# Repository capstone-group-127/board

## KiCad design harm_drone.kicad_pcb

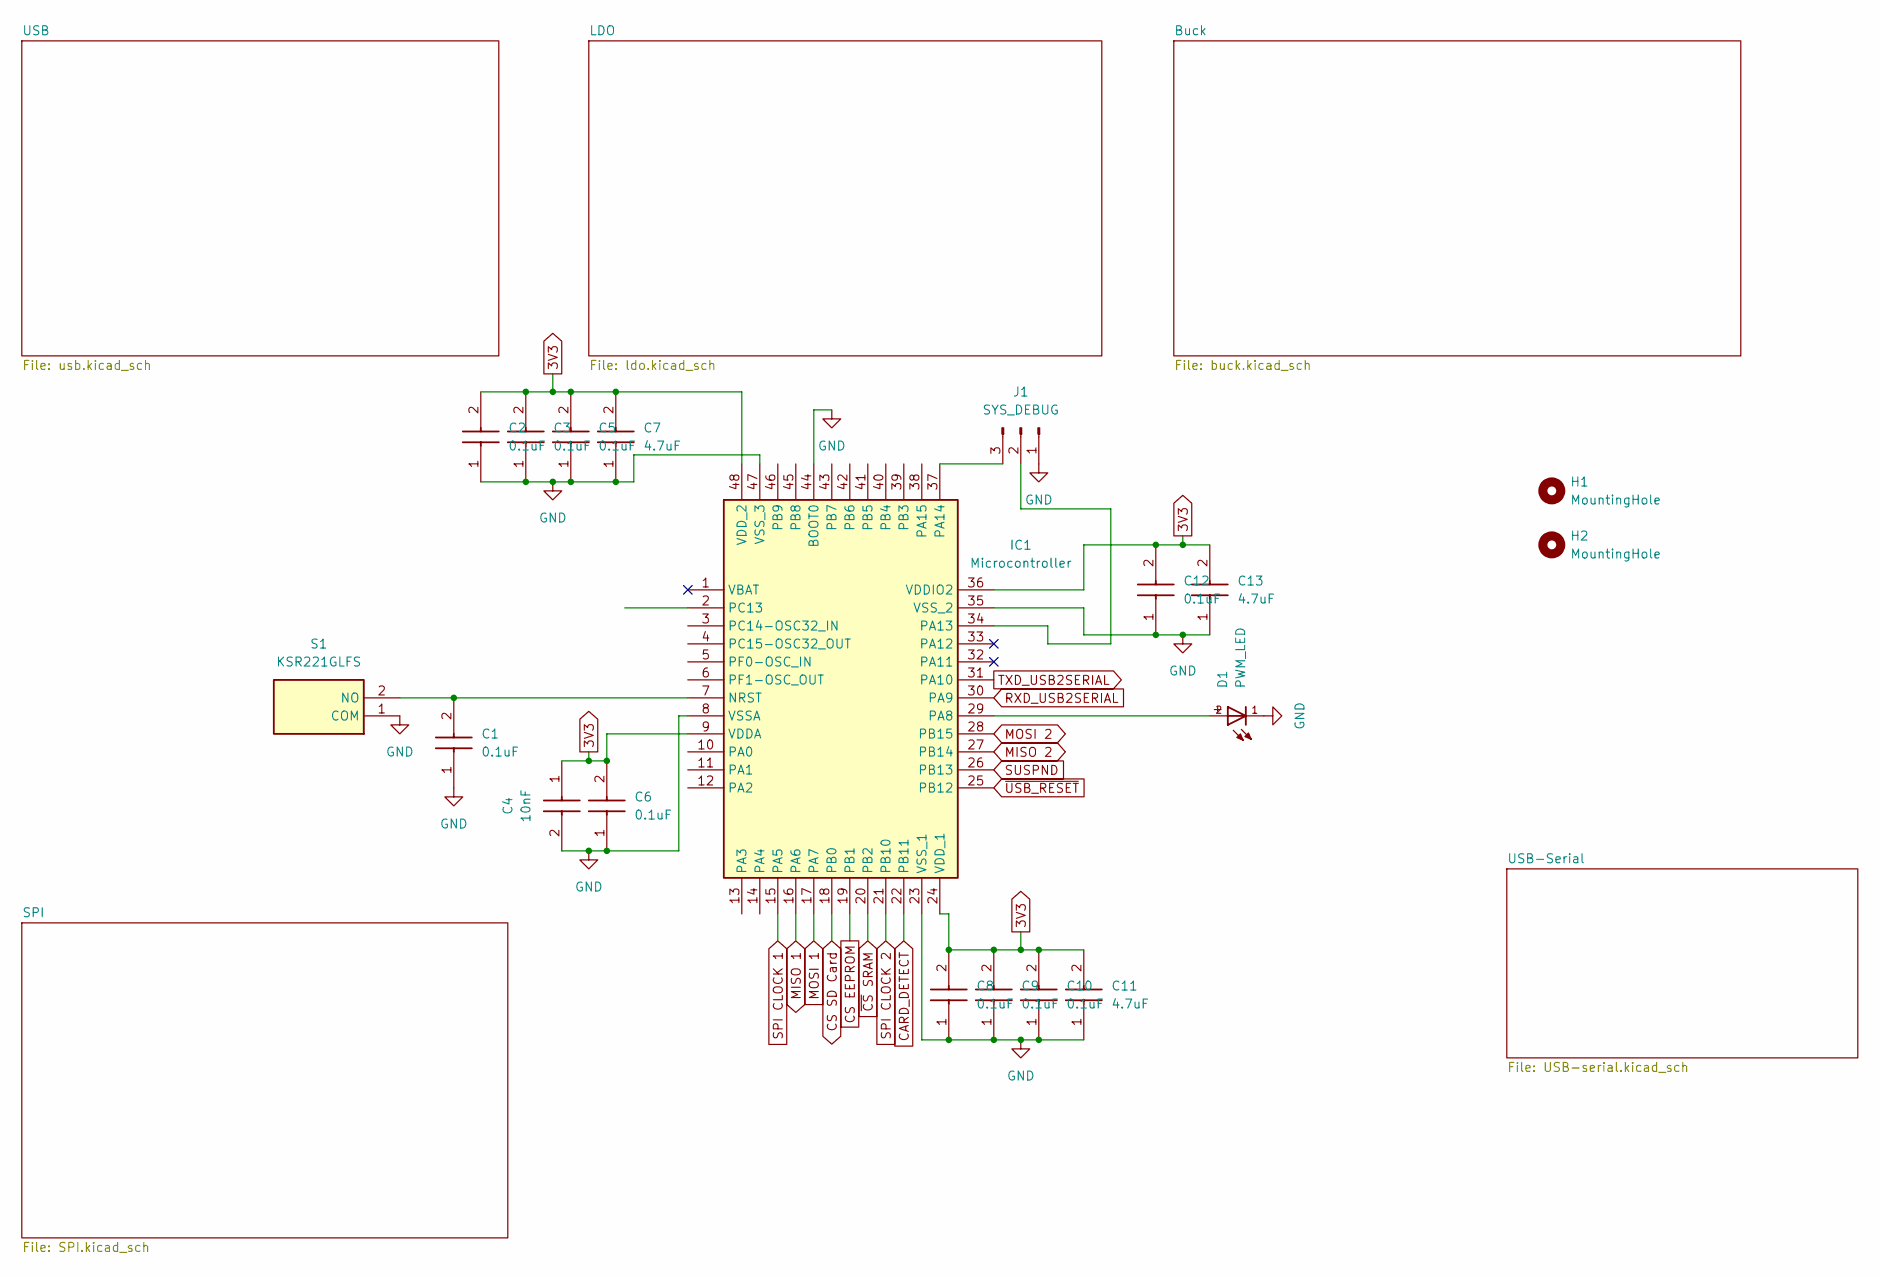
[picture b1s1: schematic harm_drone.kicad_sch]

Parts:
C1, C2, C3, C5, C6, C8, C9, C10, C12: 0.1uF; C_0805_2012Metric; Mouser Part Number 581-08055C104K
C4: 10nF; C_0805_2012Metric; Mouser Part Number 581-08055C104K
C7, C11, C13: 4.7uF; C_0805_2012Metric; Mouser Part Number 581-08055C104K
D1: PWM_LED
H1, H2: MountingHole; MountingHole_3.2mm_M3
IC1: Microcontroller; Mouser Part Number 511-STM32F072CBT6
J1: SYS_DEBUG; PinHeader_1x03_P2.54mm_Vertical
S1: KSR221GLFS; Button; Mouser Part Number 611-KSR221G-LFS

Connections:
3V3: C2.2, C3.2, C4.1, C5.2, C6.2, C7.2, C8.2, C9.2, C10.2, C11.2, C12.2, C13.2, IC1.9 (VDDA), IC1.24 (VDD_1), IC1.36 (VDDIO2), IC1.48 (VDD_2); also elsewhere on the board
CARD_DETECT: IC1.22 (PB11); also elsewhere on the board
CS EEPROM: IC1.19 (PB1); also elsewhere on the board
CS SD Card: IC1.18 (PB0); also elsewhere on the board
GND: C1.1, C2.1, C3.1, C4.2, C5.1, C6.1, C7.1, C8.1, C9.1, C10.1, C11.1, C12.1, C13.1, D1.1, IC1.8 (VSSA), IC1.23 (VSS_1), IC1.35 (VSS_2), IC1.44 (BOOT0), IC1.47 (VSS_3), J1.1, S1.1 (COM); also elsewhere on the board
MISO 1: IC1.16 (PA6); also elsewhere on the board
MISO 2: IC1.27 (PB14); also elsewhere on the board
MOSI 1: IC1.17 (PA7); also elsewhere on the board
MOSI 2: IC1.28 (PB15); also elsewhere on the board
unnamed: C1.2, IC1.7 (NRST), S1.2 (NO)
unnamed: D1.2, IC1.29 (PA8)
unnamed: IC1.34 (PA13), J1.2
unnamed: IC1.37 (PA14), J1.3
RXD_USB2SERIAL: IC1.30 (PA9); also elsewhere on the board
SPI CLOCK 1: IC1.15 (PA5); also elsewhere on the board
SPI CLOCK 2: IC1.21 (PB10); also elsewhere on the board
SUSPND: IC1.26 (PB13); also elsewhere on the board
TXD_USB2SERIAL: IC1.31 (PA10); also elsewhere on the board
~CS SRAM: IC1.20 (PB2); also elsewhere on the board
~USB_RESET: IC1.25 (PB12); also elsewhere on the board

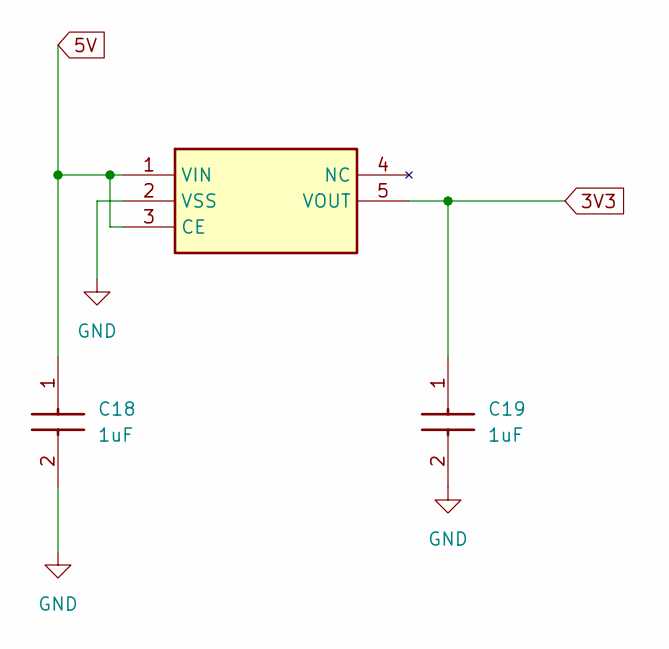
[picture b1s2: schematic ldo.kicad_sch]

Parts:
C18, C19: 1uF; C_0805_2012Metric; Mouser Part Number 581-08055C104K
IC3: LDO; Mouser Part Number 865-XC6210A332MR-G

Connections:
3V3: C19.1, IC3.5 (VOUT); also elsewhere on the board
5V: C18.1, IC3.1 (VIN), IC3.3 (CE); also elsewhere on the board
GND: C18.2, C19.2, IC3.2 (VSS); also elsewhere on the board

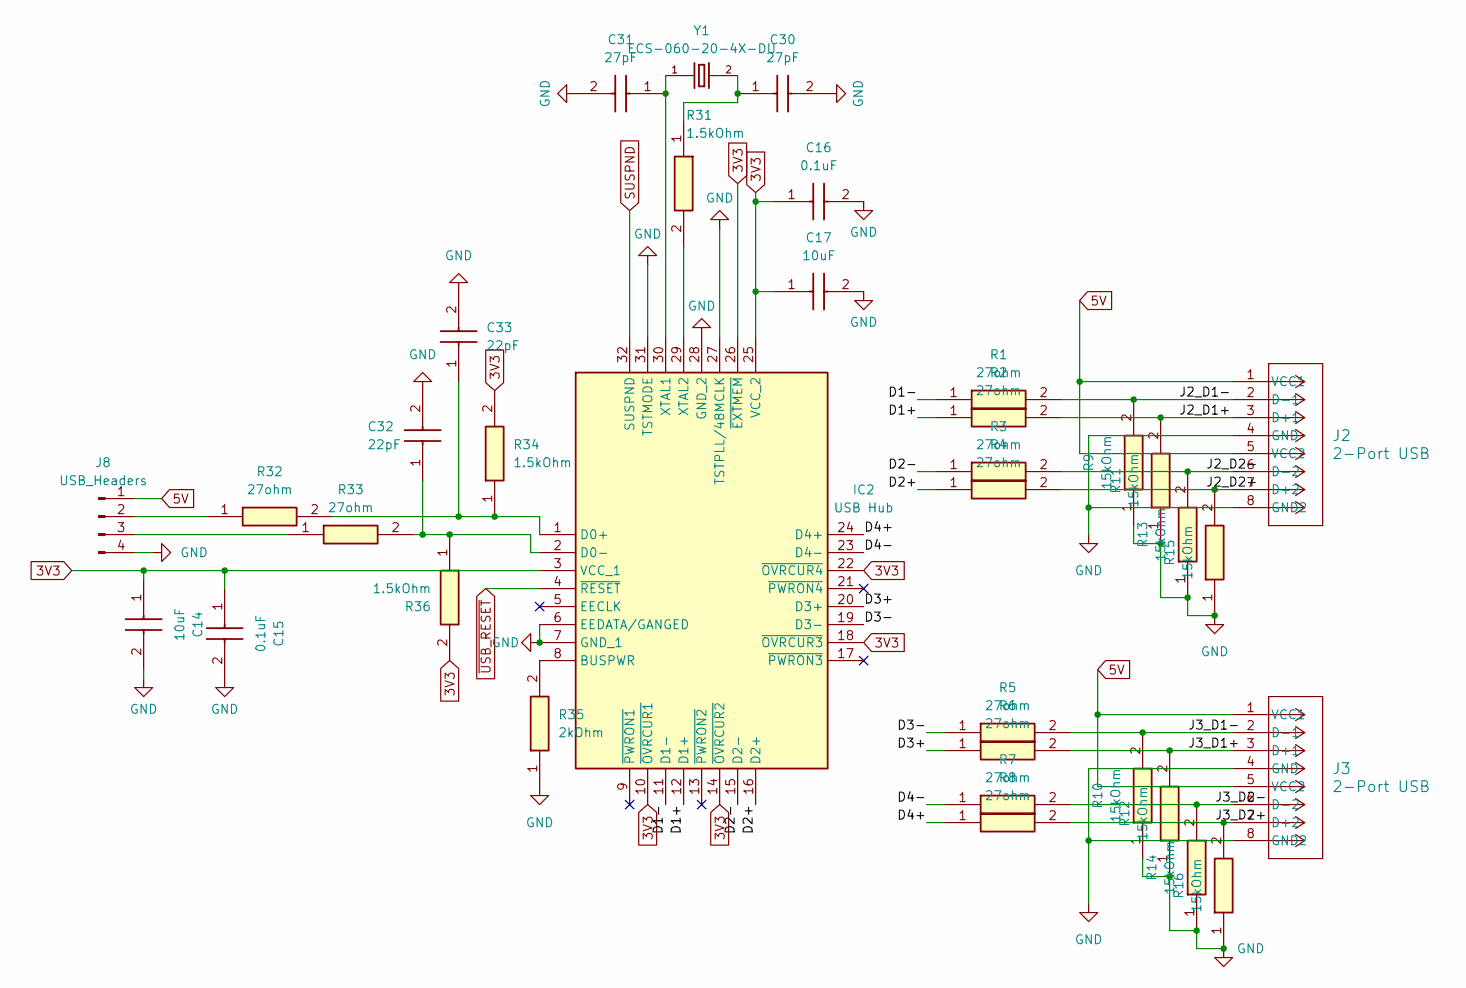
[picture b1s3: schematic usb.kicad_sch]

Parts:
C14, C17: 10uF; C_0805_2012Metric; Mouser Part Number 581-08055C104K
C15, C16: 0.1uF; C_0805_2012Metric; Mouser Part Number 581-08055C104K
C30, C31: 27pF; C_0805_2012Metric; Mouser Part Number 581-08055C104K
C32, C33: 22pF; C_0805_2012Metric; Mouser Part Number 581-08055C104K
IC2: USB Hub; USB-HUB; Mouser Part Number 595-TUSB2046IBVF
J2, J3: 2-Port USB; USBPorts
J8: USB_Headers; PinHeader_1x04_P2.54mm_Vertical
R1, R2, R3, R4, R5, R6, R7, R8, R32, R33: 27ohm; R_0805_2012Metric; Mouser Part Number 652-CR0805FX-2700ELF
R9, R10, R11, R12, R13, R14, R15, R16: 15kOhm; R_0805_2012Metric; Mouser Part Number 652-CR0805FX-2700ELF
R31, R34, R36: 1.5kOhm; R_0805_2012Metric; Mouser Part Number 652-CR0805FX-2700ELF
R35: 2kOhm; R_0805_2012Metric; Mouser Part Number 652-CR0805FX-2700ELF
Y1: ECS-060-20-4X-DU; XTAL_ECS-160-20-4X

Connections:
3V3: C14.1, C15.1, C16.1, C17.1, IC2.3 (VCC_1), IC2.10 (~OVRCUR1), IC2.14 (~OVRCUR2), IC2.18 (~OVRCUR3), IC2.22 (~OVRCUR4), IC2.25 (VCC_2), IC2.26 (~EXTMEM), R34.2, R36.2; also elsewhere on the board
5V: J2.1 (VCC1), J2.5 (VCC2), J3.1 (VCC1), J3.5 (VCC2), J8.1; also elsewhere on the board
/USB/D1+: IC2.12 (D1+), R2.1
/USB/D1-: IC2.11 (D1-), R1.1
/USB/D2+: IC2.16 (D2+), R4.1
/USB/D2-: IC2.15 (D2-), R3.1
/USB/D3+: IC2.20 (D3+), R6.1
/USB/D3-: IC2.19 (D3-), R5.1
/USB/D4+: IC2.24 (D4+), R8.1
/USB/D4-: IC2.23 (D4-), R7.1
/USB/J2_D1+: J2.3 (D+1), R2.2, R11.2
/USB/J2_D1-: J2.2 (D-1), R1.2, R9.2
/USB/J2_D2+: J2.7 (D+2), R4.2, R15.2
/USB/J2_D2-: J2.6 (D-2), R3.2, R13.2
/USB/J3_D1+: J3.3 (D+1), R6.2, R12.2
/USB/J3_D1-: J3.2 (D-1), R5.2, R10.2
/USB/J3_D2+: J3.7 (D+2), R8.2, R16.2
/USB/J3_D2-: J3.6 (D-2), R7.2, R14.2
GND: C14.2, C15.2, C16.2, C17.2, C30.2, C31.2, C32.2, C33.2, IC2.6 (EEDATA/GANGED), IC2.7 (GND_1), IC2.27 (TSTPLL/48MCLK), IC2.28 (GND_2), IC2.31 (TSTMODE), J2.4 (GND), J2.8 (GND2), J3.4 (GND), J3.8 (GND2), J8.4, R9.1, R10.1, R11.1, R12.1, R13.1, R14.1, R15.1, R16.1, R35.1; also elsewhere on the board
unnamed: C30.1, R31.1, Y1.2
unnamed: IC2.8 (BUSPWR), R35.2
unnamed: C33.1, IC2.1 (D0+), R32.2, R34.1
unnamed: C32.1, IC2.2 (D0-), R33.2, R36.1
unnamed: C31.1, IC2.30 (XTAL1), Y1.1
unnamed: IC2.29 (XTAL2), R31.2
unnamed: J8.2, R32.1
unnamed: J8.3, R33.1
SUSPND: IC2.32 (SUSPND); also elsewhere on the board
~USB_RESET: IC2.4 (~RESET); also elsewhere on the board

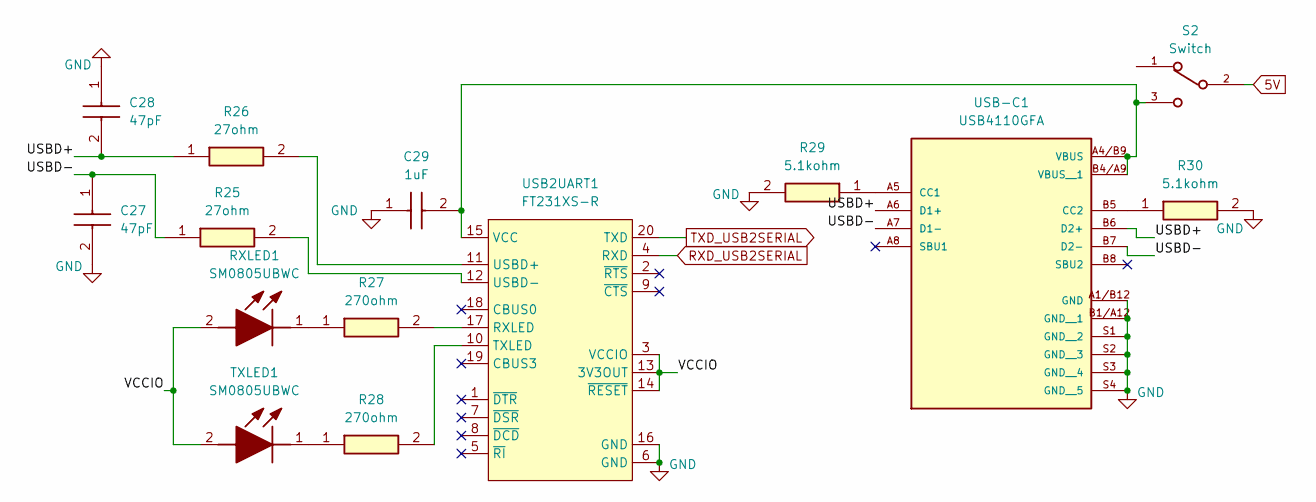
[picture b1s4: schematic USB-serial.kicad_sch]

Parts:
C27, C28: 47pF; C_0805_2012Metric; Mouser Part Number 581-08055A470J
C29: 1uF; C_0805_2012Metric; Mouser Part Number 603-CC805KRX5R6BB105
R25, R26: 27ohm; R_0805_2012Metric; Mouser Part Number 652-CR0805FX-27R0ELF
R27, R28: 270ohm; R_0805_2012Metric; Mouser Part Number 652-CR0805FX-2700ELF
R29, R30: 5.1kohm; R_0805_2012Metric; Mouser Part Number 652-CR0805FX-27R0ELF
RXLED1: SM0805UBWC; LEDC2012X110N; Mouser Part Number 749-SM0805UBWC
S2: Switch; SW_JS102011SAQN
TXLED1: SM0805UBWC; LEDC2012X110N; Mouser Part Number 749-SM0805UBWC
USB2UART1: FT231XS-R; SSOP-20_3.9x8.7mm_P0.635mm
USB-C1: USB4110GFA; GCT_USB4110GFA

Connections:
5V: S2.2; also elsewhere on the board
/USB-Serial/USBD+: C28.2, R26.1, USB-C1.A6 (D1+), USB-C1.B6 (D2+)
/USB-Serial/USBD-: C27.1, R25.1, USB-C1.A7 (D1-), USB-C1.B7 (D2-)
/USB-Serial/VCCIO: RXLED1.2 (A), TXLED1.2 (A), USB2UART1.3 (VCCIO), USB2UART1.13 (3V3OUT), USB2UART1.14 (~RESET)
GND: C27.2, C28.1, C29.1, R29.2, R30.2, USB2UART1.6 (GND), USB2UART1.16 (GND), USB-C1.A1/B12 (GND), USB-C1.B1/A12 (GND__1), USB-C1.S1 (GND__2), USB-C1.S2 (GND__3), USB-C1.S3 (GND__4), USB-C1.S4 (GND__5); also elsewhere on the board
unnamed: R27.1, RXLED1.1 (K)
unnamed: R28.1, TXLED1.1 (K)
unnamed: R27.2, USB2UART1.17 (RXLED)
unnamed: R28.2, USB2UART1.10 (TXLED)
unnamed: R26.2, USB2UART1.11 (USBD+)
unnamed: R25.2, USB2UART1.12 (USBD-)
unnamed: R29.1, USB-C1.A5 (CC1)
unnamed: R30.1, USB-C1.B5 (CC2)
unnamed: C29.2, S2.3, USB2UART1.15 (VCC), USB-C1.A4/B9 (VBUS), USB-C1.B4/A9 (VBUS__1)
RXD_USB2SERIAL: USB2UART1.4 (RXD); also elsewhere on the board
TXD_USB2SERIAL: USB2UART1.20 (TXD); also elsewhere on the board

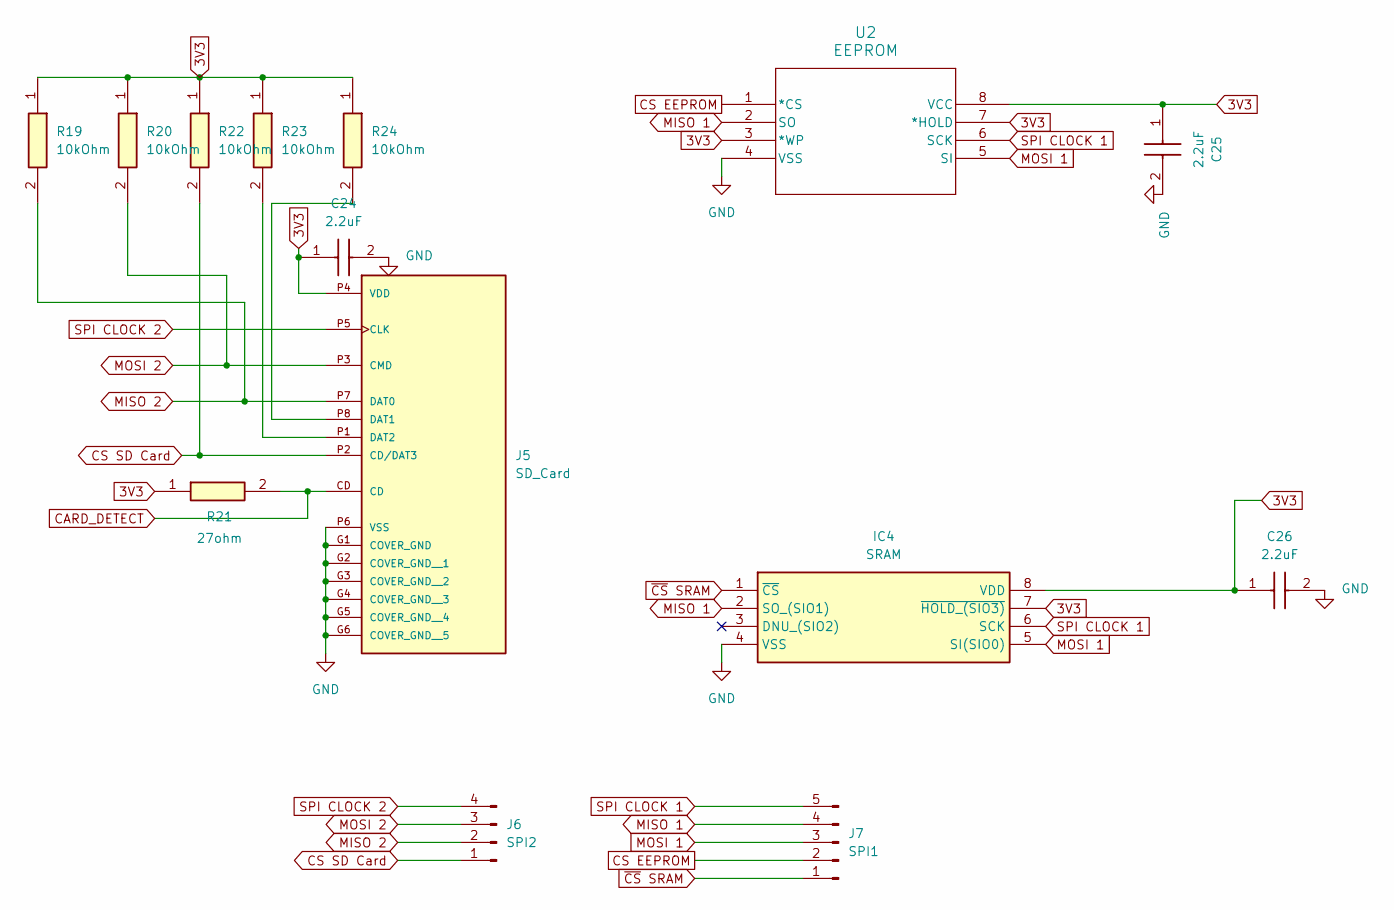
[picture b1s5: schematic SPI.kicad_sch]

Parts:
C24, C25, C26: 2.2uF; C_0805_2012Metric; Mouser Part Number 581-08055C104K
IC4: SRAM; Mouser Part Number 870-62WS2568GBL4NLIT
J5: SD_Card; SDCard; PARTREV 1.0
J6: SPI2; PinHeader_1x04_P2.54mm_Vertical
J7: SPI1; PinHeader_1x05_P2.54mm_Vertical
R19, R20, R22, R23, R24: 10kOhm; R_0805_2012Metric; Mouser Part Number 652-CR0805FX-2700ELF
R21: 27ohm; R_0805_2012Metric; Mouser Part Number 652-CR0805FX-2700ELF
U2: EEPROM

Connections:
3V3: C24.1, C25.1, C26.1, IC4.7 (~HOLD_(SIO3)), IC4.8 (VDD), J5.P4 (VDD), R19.1, R20.1, R21.1, R22.1, R23.1, R24.1, U2.3 (*WP), U2.7 (*HOLD), U2.8 (VCC); also elsewhere on the board
CARD_DETECT: J5.CD, R21.2; also elsewhere on the board
CS EEPROM: J7.2, U2.1 (*CS); also elsewhere on the board
CS SD Card: J5.P2 (CD/DAT3), J6.1, R22.2; also elsewhere on the board
GND: C24.2, C25.2, C26.2, IC4.4 (VSS), J5.G1 (COVER_GND), J5.G2 (COVER_GND__1), J5.G3 (COVER_GND__2), J5.G4 (COVER_GND__3), J5.G5 (COVER_GND__4), J5.G6 (COVER_GND__5), J5.P6 (VSS), U2.4 (VSS); also elsewhere on the board
MISO 1: IC4.2 (SO_(SIO1)), J7.4, U2.2 (SO); also elsewhere on the board
MISO 2: J5.P7 (DAT0), J6.2, R19.2; also elsewhere on the board
MOSI 1: IC4.5 (SI(SIO0)), J7.3, U2.5 (SI); also elsewhere on the board
MOSI 2: J5.P3 (CMD), J6.3, R20.2; also elsewhere on the board
unnamed: J5.P8 (DAT1), R24.2
unnamed: J5.P1 (DAT2), R23.2
SPI CLOCK 1: IC4.6 (SCK), J7.5, U2.6 (SCK); also elsewhere on the board
SPI CLOCK 2: J5.P5 (CLK), J6.4; also elsewhere on the board
~CS SRAM: IC4.1 (~CS), J7.1; also elsewhere on the board

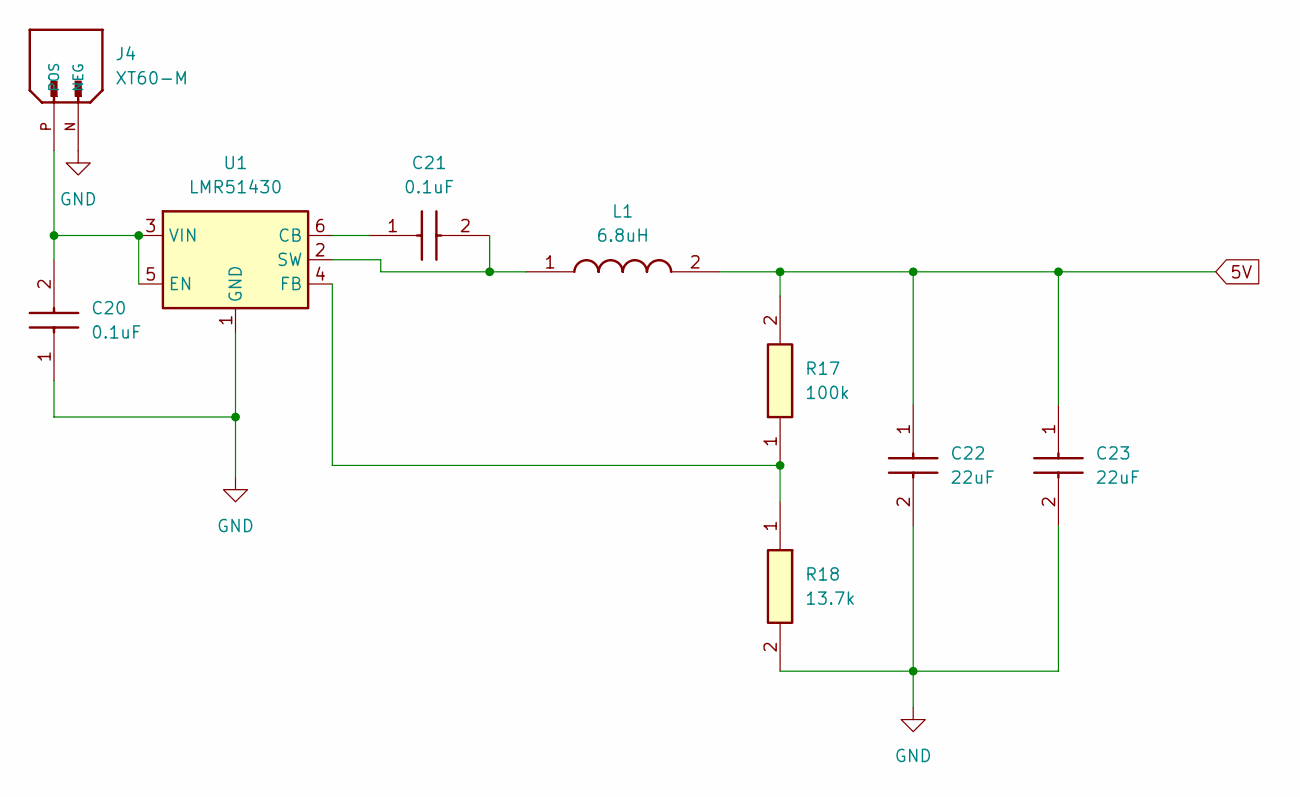
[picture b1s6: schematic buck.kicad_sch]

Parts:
C20, C21: 0.1uF; C_0805_2012Metric; Mouser Part Number 581-08055C104K
C22, C23: 22uF; C_0805_2012Metric; Mouser Part Number 581-08055C104K
J4: XT60-M; PARTREV V1.2
L1: 6.8uH; Inductor; Mouser Part Number 710-7447707068
R17: 100k; R_0805_2012Metric; Mouser Part Number 652-CR0805FX-2700ELF
R18: 13.7k; R_0805_2012Metric; Mouser Part Number 652-CR0805FX-2700ELF
U1: LMR51430; SOT-23-6

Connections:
5V: C22.1, C23.1, L1.2, R17.2; also elsewhere on the board
GND: C20.1, C22.2, C23.2, J4.N (NEG), R18.2, U1.1 (GND); also elsewhere on the board
unnamed: C20.2, J4.P (POS), U1.3 (VIN), U1.5 (EN)
unnamed: C21.1, U1.6 (CB)
unnamed: R17.1, R18.1, U1.4 (FB)
unnamed: C21.2, L1.1, U1.2 (SW)

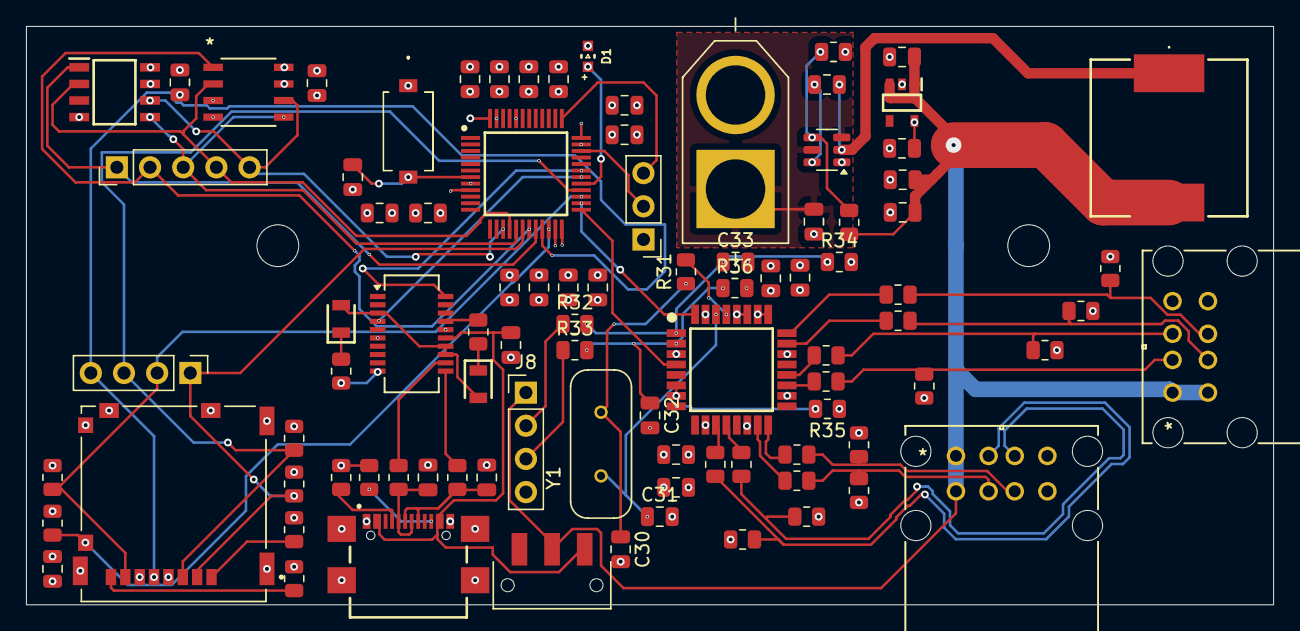
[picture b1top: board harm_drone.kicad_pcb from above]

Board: 4 copper layers, 95.5 x 44.3 mm, 94 parts (0 on the bottom side), 63 nets.

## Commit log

2024-12-18 empty KiCad project
2024-12-18 create subsystems
2024-12-18 keeping track of our resources
2024-12-18 symbol and footprint libraries
2024-12-18 Added Symbols and Buck Converter
2025-01-05 Add SD card
    SD card footprint
2025-01-05 Add EEPROM
    Added EEPROM footprint
2025-01-05 Rename SD card and EEPROM
    Renamed symbols
2025-01-05 Added SRAM
    Added SRAM
2025-01-05 merged in USB
2025-01-05 USB-Serial Sheet Add
2025-01-05 usb serial additions
2025-01-05 SPI support
    Implemented SPI support
2025-01-12 Added Uc
2025-01-12 LDO changes from camryn
2025-01-12 New gnd symbol
    Changed ground symbol in LDO
2025-01-12 merged Mike's USB-serial changes
2025-01-12 Put grounds on SPI
    Changed ground net to symbols
2025-01-12 Power and ground added on microcontroller
    Added power and ground to microcontroller
2025-01-12 Added SPI grounds
    SPI ground added
2025-01-12 usb hub support completed
2025-01-12 standardize 5V and 3V3 labels
2025-01-12 Updated SPI/Microcontroller
    Updated SPI schematic and connected to microcontroller
2025-01-12 finished up schematic
2025-01-12 more footprint updates
2025-01-13 initial PCB draft!
2025-01-15 before differential routing
2025-01-15 namespace change
2025-01-30 add PWM LED
2025-01-30 Fixed PCB mistakes
    Moved Vias and one trace
2025-02-02 before model updates
2025-02-02 link new models
2025-02-02 final sd card model
2025-02-03 schematic fixes are done
2025-02-05 final changes
2025-03-13 Rotating
    Changed rotation from 0 to 360
2025-03-13 USB stack changes
2025-03-16 building on GitHub actions?
2025-03-16 Revert "building on GitHub actions?"
    This reverts commit 608c3f9d32cbe9cba69a69d90418f8bf264bc07c.
2025-03-30 final changes to 3d models
2025-04-08 USB fixes
2025-04-17 overcurrent fixes
2025-04-17 gitignore
2025-05-08 New vias
    Added new vias
